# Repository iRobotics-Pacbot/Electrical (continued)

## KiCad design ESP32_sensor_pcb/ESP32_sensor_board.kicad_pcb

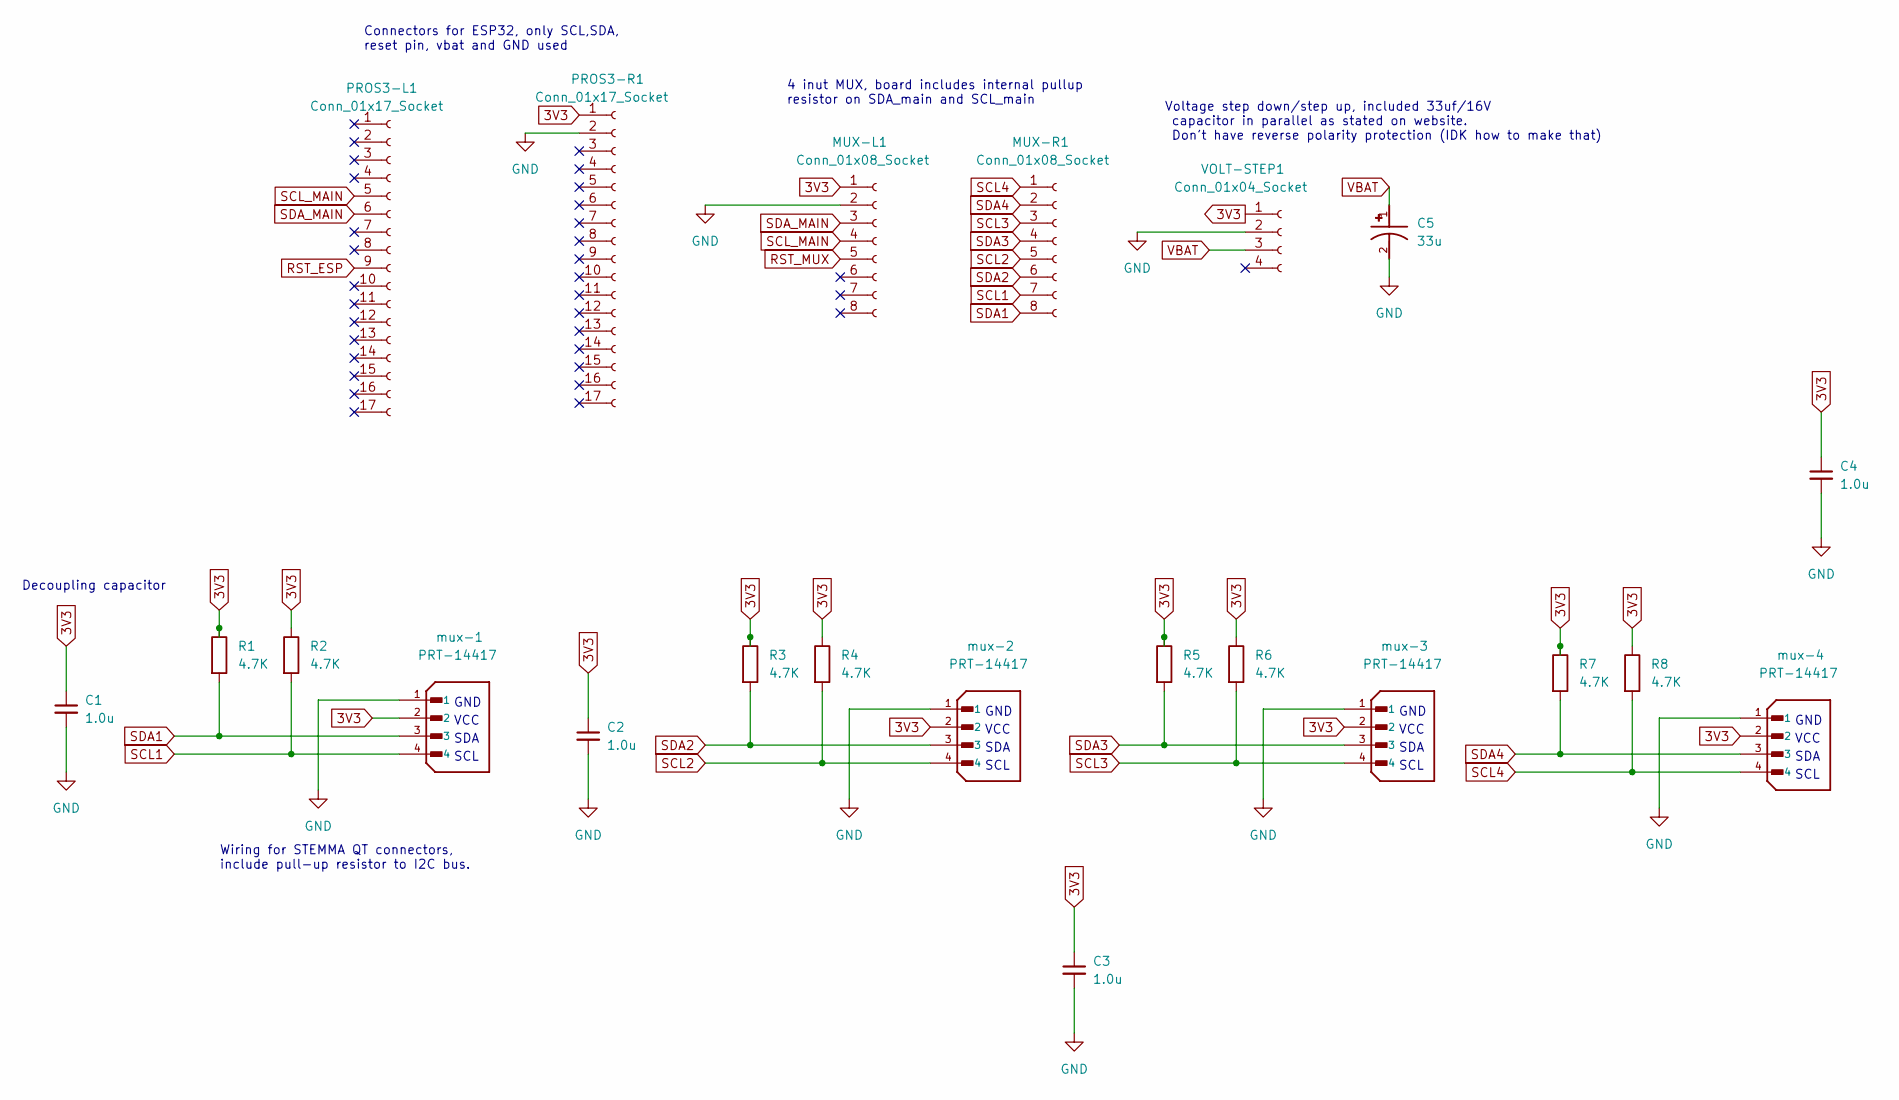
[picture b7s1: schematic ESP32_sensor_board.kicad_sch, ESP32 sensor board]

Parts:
C1, C2, C3, C4: 1.0u; C_01005_0402Metric
C5: 33u; CAP_16TQC33MYFD; PARTREV 30-Nov-20
MUX-L1: Conn_01x08_Socket; PinSocket_1x08_P2.54mm_Vertical
MUX-R1: Conn_01x08_Socket; PinSocket_1x08_P2.54mm_Vertical
PROS3-L1, PROS3-R1: Conn_01x17_Socket; PinSocket_1x17_P2.54mm_Vertical
R1, R2, R3, R4, R5, R6, R7, R8: 4.7K; R_0603_1608Metric
VOLT-STEP1: Conn_01x04_Socket; PinSocket_1x04_P2.54mm_Vertical
mux-1, mux-2, mux-3, mux-4: PRT-14417; SPARKFUN_PRT-14417; PARTREV NA

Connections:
3V3: C1.1, C2.1, C3.1, C4.1, MUX-L1.1, PROS3-R1.1, R1.1, R2.1, R3.1, R4.1, R5.1, R6.1, R7.1, R8.1, VOLT-STEP1.1, mux-1.2, mux-2.2, mux-3.2, mux-4.2
GND: C1.2, C2.2, C3.2, C4.2, C5.2, MUX-L1.2, PROS3-R1.2, VOLT-STEP1.2, mux-1.1, mux-2.1, mux-3.1, mux-4.1
RST_ESP: PROS3-L1.9
RST_MUX: MUX-L1.5
SCL1: MUX-R1.7, R2.2, mux-1.4
SCL2: MUX-R1.5, R4.2, mux-2.4
SCL3: MUX-R1.3, R6.2, mux-3.4
SCL4: MUX-R1.1, R8.2, mux-4.4
SCL_MAIN: MUX-L1.4, PROS3-L1.5
SDA1: MUX-R1.8, R1.2, mux-1.3
SDA2: MUX-R1.6, R3.2, mux-2.3
SDA3: MUX-R1.4, R5.2, mux-3.3
SDA4: MUX-R1.2, R7.2, mux-4.3
SDA_MAIN: MUX-L1.3, PROS3-L1.6
VBAT: C5.1, VOLT-STEP1.3

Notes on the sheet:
SDA
Connectors for ESP32, only SCL,SDA, reset pin, vbat and GND used
GND
VCC
Decoupling capacitor
4 inut MUX, board includes internal pullup resistor on SDA_main and SCL_main
Wiring for STEMMA QT connectors, include pull-up resistor to I2C bus.
SCL
Voltage step down/step up, included 33uf/16V capacitor in parallel as stated on website. Don't have reverse polarity protection (IDK how to make that)

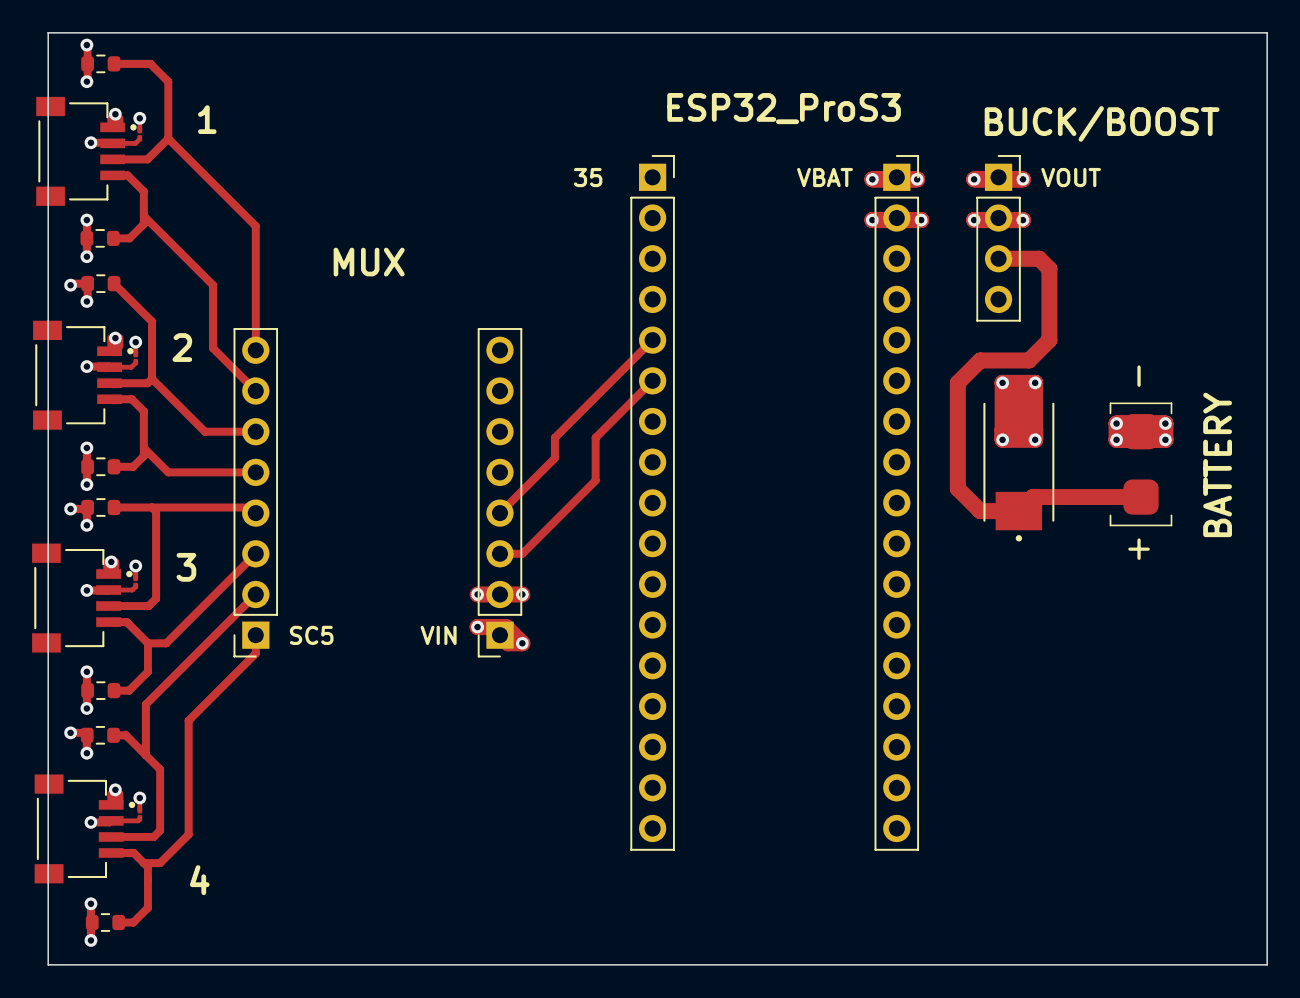
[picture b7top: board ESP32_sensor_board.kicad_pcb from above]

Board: 4 copper layers, 76.1 x 58.2 mm, 22 parts (0 on the bottom side), 13 nets.

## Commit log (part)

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2023-11-19 start making lighting pcb schematic
2023-11-22 cv lighting schematic
2023-11-22 removing this extra file
2023-11-22 formatting changes
2023-12-01 cv lighting schematic almost done, footprints all there
2023-12-01 added some notes to schematic
2023-12-03 Added some changes
2023-12-04 updates to lighting pcb
2023-12-07 initial routing and edge cuts for pcb
2023-12-11 updates to lighting pcb, now smaller
2023-12-11 changes to lighting pcb
2023-12-18 modified leds a bit
2023-12-19 modified leds a bit more
2024-01-04 more changes to lighting pcb
2024-01-16 more changes to cv lighting
2024-01-16 changes to cv lighting
2024-01-17 more changes to cv lighting for like the 100th time
2024-01-18 cv lighting final?
2024-01-19 [Generated Gerber Files and Drill Files]
2024-01-21 [BOM files are really boom]
2024-01-21 added ordering pcb files
2024-01-22 leftover things not committed; pcb ordered!
2024-03-09 include new pacbot board kicad file
2024-03-18 schematic done(?) and layout
2024-03-24 routing to pcb
2024-09-14 updating electrical 2023-2024 repository with cv lighting and pacbot pcb
2024-09-14 adding 2023 pacbot pcb
2024-09-16 making new kicad project
2024-09-16 Create new power management circuit folder
2024-09-16 Backlink to CADLAB.io has been added.
2024-09-16 adding symbol library to new project
2024-09-17 updating symbol library
2024-09-23 pcb attempt
2024-09-23 KiCad PCB Attempt
2024-09-30 updated board design
2024-10-05 Changed motor controller schematic
2024-10-05 battery management schematic
2024-10-05 schematic updated
2024-10-06 Battery Management Circuit Prototype
2024-10-15 updated schematic with neopixels and other feedback
2024-10-15 pushing battery management design with relay
2024-10-19 updated schematic and some footprints, now 6 tofs with interrupts
2024-10-21 updating
2024-10-26 PCB design
2024-10-26 some changes to pcb
2024-11-05 uncommited changes
2024-11-08 Changed layout to account for battery and motors, tried routing stuff
2024-11-12 new chassis shape
2024-11-16 changed PCB dimensions
2024-11-16 changed motor dimensions
2024-11-16 changed layout
2024-11-19 Layout
2024-11-19 layout updated
2024-11-21 updated pcb layout, pros3 has pads
2024-11-25 minor changes
2025-01-09 PCB with routing
2025-01-14 added testpoints
2025-01-25 some more changes
2025-01-26 fixed neopixels, all ready to go?
2025-01-26 some minor changes to traces
2025-01-26 some more minor adjustments
2025-01-26 some more misc changes
2025-01-26 some more tiny changes
2025-01-28 jonathan change bms
2025-01-28 updated bms schematic and layout
2025-01-28 final changes, pcb ordered
2025-02-01 new bms design
2025-09-28 adding example pcb project
2025-10-03 Created MainPCB
2025-10-03 Created symbol for CJ3139K mosfet
2025-10-05 Added specific values for in/out capacitors
2025-10-12 Added footprints
2025-10-26 making a folder
2025-10-26 Uploading the pcb doc
2025-10-26 schematic from 10/19
